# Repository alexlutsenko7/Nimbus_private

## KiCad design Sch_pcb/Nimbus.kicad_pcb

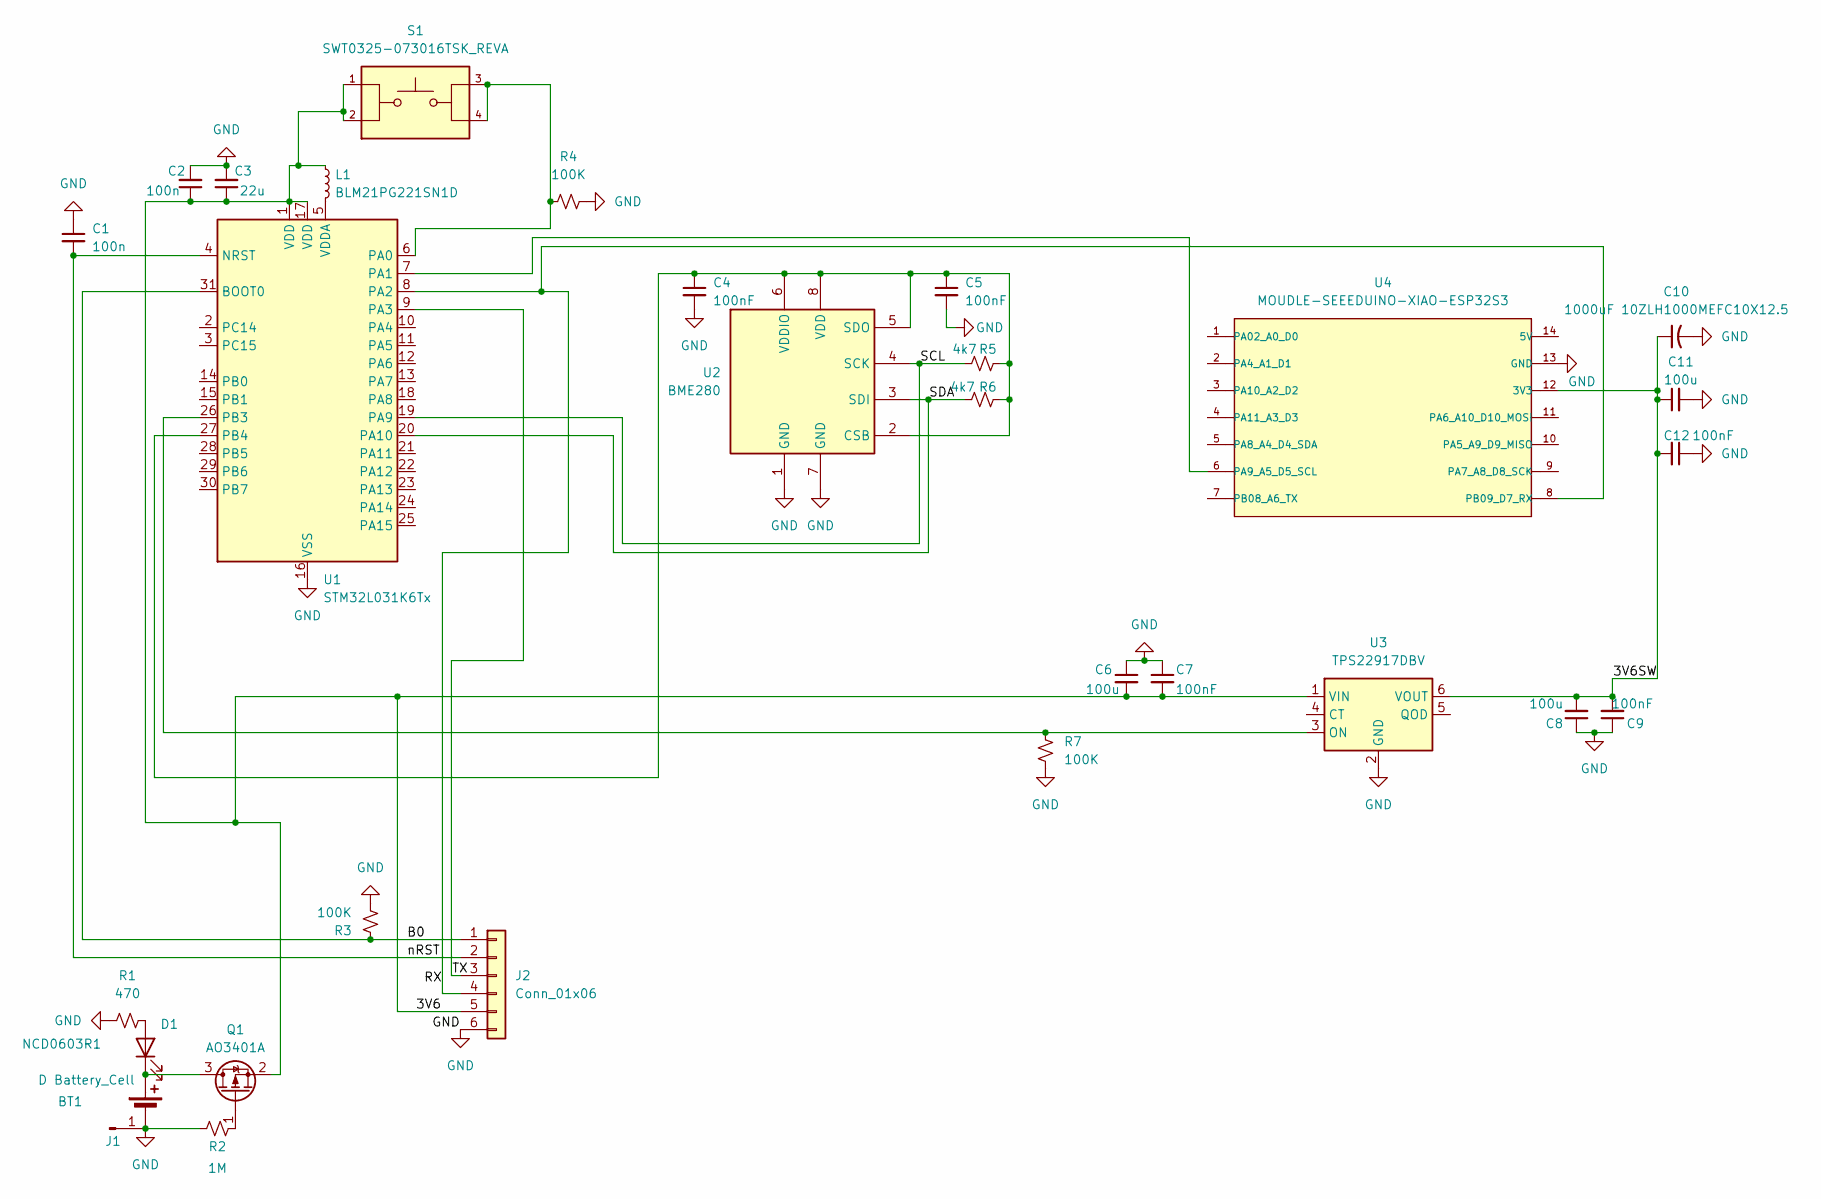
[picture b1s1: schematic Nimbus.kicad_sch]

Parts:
BT1: D Battery_Cell; PinHeader_1x02_P2.54mm_Vertical
C1, C2: 100n; C_0603_1608Metric_Pad1.08x0.95mm_HandSolder
C3: 22u; C_0603_1608Metric_Pad1.08x0.95mm_HandSolder
C4, C5: 100nF; C_0603_1608Metric_Pad1.08x0.95mm_HandSolder
C6, C8: 100u; C_1206_3216Metric_Pad1.33x1.80mm_HandSolder
C7, C9, C12: 100nF; C_0603_1608Metric
C10: 1000uF 10ZLH1000MEFC10X12.5; CAP_10X12.5_RUB
C11: 100u; C_1206_3216Metric
D1: NCD0603R1; D_0603_1608Metric
J1: GND; TestPoint_Pad_1.0x1.0mm
J2: Conn_01x06; PinHeader_1x06_P2.54mm_Vertical
L1: BLM21PG221SN1D; L_0805_2012Metric_Pad1.05x1.20mm_HandSolder
Q1: AO3401A; SOT-23
R1: 470; R_0603_1608Metric_Pad0.98x0.95mm_HandSolder
R2: 1M; R_0603_1608Metric_Pad0.98x0.95mm_HandSolder
R3, R4, R7: 100K; R_0603_1608Metric_Pad0.98x0.95mm_HandSolder
R5, R6: 4k7; R_0603_1608Metric_Pad0.98x0.95mm_HandSolder
S1: SWT0325-073016TSK_REVA; SW_SWT0325-073016TSK_REVA; PARTREV A
U1: STM32L031K6Tx; LQFP-32_7x7mm_P0.8mm
U2: BME280; Bosch_LGA-8_2.5x2.5mm_P0.65mm_ClockwisePinNumbering
U3: TPS22917DBV; SOT-23-6
U4: MOUDLE-SEEEDUINO-XIAO-ESP32S3; AlxXIAO_MOUDLE14P-SMD-2.54-21X17.8MM

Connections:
/3V6: C2.1, C3.1, C6.2, C7.2, J2.5, L1.1, Q1.2 (S), S1.1, S1.2, U1.1 (VDD), U1.17 (VDD), U3.1 (VIN)
/3V6SW: C8.2, C9.2, C10.1, C11.1, C12.2, U3.6 (VOUT), U4.12 (3V3)
/B0: J2.1, R3.1, U1.31 (BOOT0)
/RX: J2.4, U1.8 (PA2), U4.8 (PB09_D7_RX)
/SCL: R5.1, U1.19 (PA9), U2.4 (SCK)
/SDA: R6.1, U1.20 (PA10), U2.3 (SDI)
/TX: J2.3, U1.9 (PA3)
/nRST: C1.2, J2.2, U1.4 (NRST)
GND: BT1.2 (-), C1.1, C2.2, C3.2, C4.2, C5.2, C6.1, C7.1, C8.1, C9.1, C10.2, C11.2, C12.1, J1.1 (Pin_1_1), J2.6, R1.1, R2.1, R3.2, R4.2, R7.2, U1.16 (VSS), U1.32 (VSS), U2.1 (GND), U2.7 (GND), U3.2 (GND), U4.13 (GND)
unnamed: BT1.1 (+), D1.1 (K), Q1.3 (D)
unnamed: D1.2 (A), R1.2
unnamed: Q1.1 (G), R2.2
unnamed: R4.1, S1.3, S1.4, U1.6 (PA0)
unnamed: U1.7 (PA1), U4.6 (PA9_A5_D5_SCL)
unnamed: R7.1, U1.26 (PB3), U3.3 (ON)
unnamed: C4.1, C5.1, R5.2, R6.2, U1.27 (PB4), U2.2 (CSB), U2.5 (SDO), U2.6 (VDDIO), U2.8 (VDD)
unnamed: L1.2, U1.5 (VDDA)

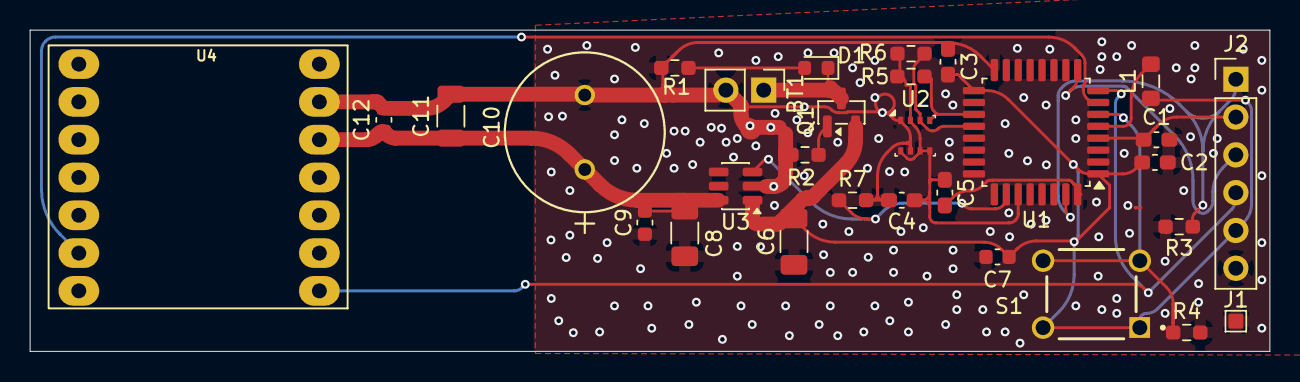
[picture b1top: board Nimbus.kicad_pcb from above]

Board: 2 copper layers, 83.3 x 21.6 mm, 30 parts (0 on the bottom side), 17 nets.

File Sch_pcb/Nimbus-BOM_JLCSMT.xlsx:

Comment | Designator | Footprint | JLCPCB Part #（optional）
100nF | C1, C2, C4, C5, C7, C9, C12 | C_0603_1608Metric | C1591
100uF | C6, C8, C11 | C_1206_3216Metric | C312983
22uF | C3 | C_0603_1608Metric | C84419
1000uF | C10 | CAP_10 | C43339
100k | R3, R4, R7 | R_0603_1608Metric | C14675
4k7 | R5, R6 | R_0603_1608Metric | C25999
470 | R1 | R_0603_1608Metric | C177286
1M | R2 | R_0603_1608Metric | C177344
Ferrite Bead 0805 | L1 | L_0805 | C85840
LED NCD0603R1 | D1 | D_0603_1608Metric | C84263
TPS22917DBV | U3 | SOT-23-6 | C2680344
STM32L031K6T6TR | U1 | LQFP-32(7x7) | C94085
BME280 | U2 | LGA-8(2.5x2.5) | C92489
AO3401A | Q1 | SOT-23 | C15127
